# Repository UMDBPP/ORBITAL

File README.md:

# ORBITAL
Stablization System plus more

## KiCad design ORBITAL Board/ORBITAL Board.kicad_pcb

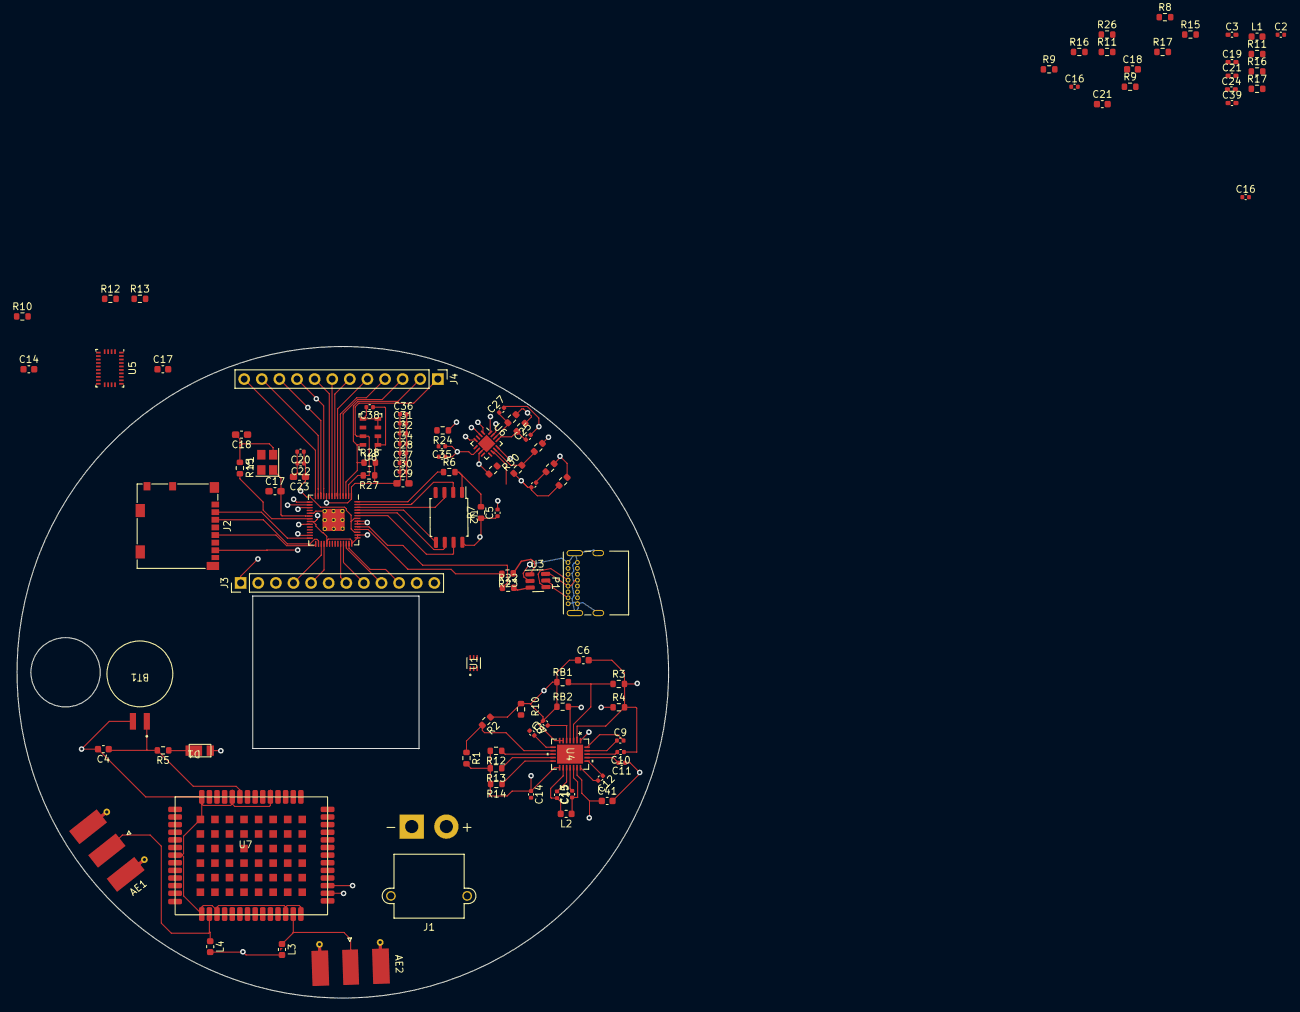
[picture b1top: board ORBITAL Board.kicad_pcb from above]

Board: 4 copper layers, 94.0 x 94.0 mm, 107 parts (0 on the bottom side), 93 nets.

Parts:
AE1, AE2: Antenna; SMA_Molex_73251-1153_EdgeMount_Horizontal
BT1: MS920SE; BT1
C1: 22n; C_0402_1005Metric
C2: 10u; C_0402_1005Metric
C3, C24, C39: 100n; C_0402_1005Metric_Pad0.74x0.62mm_HandSolder
C4: 1u; C_0603_1608Metric
C5, C13, C15, C16#2, C20, C22, C28, C30, C31, C32, C34, C36, C37, C38: 100n; C_0402_1005Metric
C6, C41: 22u; C_0603_1608Metric
C7: 4.7u; C_0402_1005Metric
C8: 1.8n; C_0402_1005Metric
C9, C12, C25: 10n; C_0402_1005Metric
C10, C11: 47n; C_0402_1005Metric
C14: 100u; C_0402_1005Metric
C14#2: 10u; C_0603_1608Metric
C16: 22U; C_0402_1005Metric
C17, C18#2: 22p; C_0603_1608Metric
C17#2, C18: 27p; C_0603_1608Metric_Pad1.08x0.95mm_HandSolder
C19: 22p; C_0402_1005Metric_Pad0.74x0.62mm_HandSolder
C21: 22u; C_0402_1005Metric_Pad0.74x0.62mm_HandSolder
C21#2: 2.2u; C_0603_1608Metric
C23, C29: 1u; C_0603_1608Metric_Pad1.08x0.95mm_HandSolder
C27: 1n; C_0402_1005Metric
C33: 2.2u; C_0402_1005Metric
C35: 22u; C_0402_1005Metric
D1: D_Zener; DFLS130L
J1: Conn_01x02; AMASS_XT30PW-M_1x02_P2.50mm_Horizontal
J2: Micro_SD_Card_Det; microSD_HC_Molex_104031-0811
J3, J4: Conn_01x12; PinHeader_1x12_P2.54mm_Vertical
L1: 4.7u; L_0603_1608Metric
L2: 3.3u; L_0603_1608Metric
L3, L4: 39n; L_0603_1608Metric
P1: USB_C_Plug_USB2.0; USB_C_Receptacle_GCT_USB4085
R1: 500K; R_0603_1608Metric
R2, R16: 100K; R_0603_1608Metric
R3: 350K; R_0603_1608Metric
R4: 510K; R_0603_1608Metric
R5: 620; R_0603_1608Metric
R6, R15#2: 1k; R_0603_1608Metric
R7, R9#2, R17#2, R26, R27, R28: 10k; R_0603_1608Metric
R8, R9: 5.1k; R_0603_1608Metric
R10: 40.2K; R_0603_1608Metric
R10#2, R11, R12#2, R13#2: 2.2k; R_0603_1608Metric
R11#2: 225k; R_0603_1608Metric
R12, R13, R14: 5.1K; R_0603_1608Metric
R15: 1M; R_0603_1608Metric
R16#2: 715k; R_0603_1608Metric
R17: 50k; R_0603_1608Metric
R18, R19: 18; R_0603_1608Metric
R20: 1K; R_0603_1608Metric
R21: 47K; R_0603_1608Metric
R22, R23: 27.4; R_0603_1608Metric
R24, R25: .33; R_0603_1608Metric
R29: 9000; R_0603_1608Metric
R30: 2000; R_0603_1608Metric
RB1, RB2: 100K; R_0603_1608Metric
U1: PTPS563206DRLR; SOT_07SDRLR_TEX
U2: W25Q128JVS; SOIC-8_5.23x5.23mm_P1.27mm
U3: USBLC6-2SC6; SOT-23-6
U4: LTC3118
U5: BNO085; LGA-28_5.2x3.8mm_P0.5mm
U5#2: RP2040; RP2040-QFN-56
U6: STSPIN220; VQFN-16-1EP_3x3mm_P0.5mm_EP1.8x1.8mm
U7: PX1172RH
U8: MS5607-02BA; LGA-8_3x5mm_P1.25mm
Y1: ABLS-12.000MHZ-B4-T; Crystal_SMD_Abracon_ABM8G-4Pin_3.2x2.5mm

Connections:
+1V1: C20.1, C22.1, C23.1, R29.2, U5#2.23 (DVDD), U5#2.45 (VREG_VOUT), U5#2.50 (DVDD)
+3.3V: C5.1, C19.1, C21.2, C24.2, C28.1, C29.1, C30.1, C31.1, C32.1, C34.1, C36.1, C37.1, C38.1, J2.4 (VDD), L1.2, L3.2, L4.2, R7.1, R11#2.2, R18.2, R19.2, R27.1, R28.2, U2.8 (VCC), U5#2.1 (IOVDD), U5#2.10 (IOVDD), U5#2.22 (IOVDD), U5#2.33 (IOVDD), U5#2.42 (IOVDD), U5#2.43 (ADC_AVDD), U5#2.44 (VREG_IN), U5#2.48 (USB_VDD), U5#2.49 (IOVDD), U7.33 (VDD33), U7.34 (VDD33), U8.1 (VDD), U8.2 (PS)
+3V3: D1.2 (A), J3.12, R9#2.1, R10#2.2, R11.1, R12#2.2, R13#2.1, R17#2.1, R26.1, U5.3 (VDD), U5.28 (VDDIO)
+6V: C2.2, C14.1, C33.1, C35.1, C39.1, R1.2, R12.2, R13.2, R14.2, R16.2, U1.1 (VIN), U4.13 (VOUT), U6.6 (VS)
+BATT: C16.2, C41.1, J1.2, U4.18 (VIN2)
/A0: J3.7, U5#2.38 (GPIO26_ADC0)
/A1: J3.8, U5#2.39 (GPIO27_ADC1)
/A2: J3.9, U5#2.40 (GPIO28_ADC2)
/A3: J3.10, U5#2.41 (GPIO29_ADC3)
/D0: J4.1, R27.2, U5#2.2 (GPIO0), U8.7 (SDI/SDA)
/D1: J4.2, R28.1, U5#2.3 (GPIO1), U8.8 (SCLK)
/D2: J4.3, U5#2.4 (GPIO2), U6.16 (MODE1)
/D3: J4.4, U5#2.5 (GPIO3), U6.15 (MODE2)
/D4: J4.5, U5#2.6 (GPIO4), U6.1 (DIR)
/D5: J4.6, U5#2.7 (GPIO5), U6.2 (STCK)
/D6: J4.7, U5#2.8 (GPIO6)
/D7: J4.8, U5#2.9 (GPIO7)
/D8: J4.9, U5#2.11 (GPIO8), U7.16 (RXD_R)
/D9: J4.10, U5#2.12 (GPIO9), U7.17 (TXD_R)
/D10: J4.11, U5#2.13 (GPIO10)
/D11: J4.12, U5#2.14 (GPIO11)
/D12: J3.1, U5#2.15 (GPIO12)
/D13: J3.2, U5#2.16 (GPIO13)
/D14: J3.3, U5#2.17 (GPIO14)
/D15/CLK IN: J3.4, U5#2.31 (GPIO20)
/D16/CLK OUT: J3.5, U5#2.32 (GPIO21)
/D+: R22.2, U3.3 (I/O2)
/D-: R23.1, U3.1 (I/O1)
/QSPI_SCLK: U2.6 (CLK), U5#2.52 (QSPI_SCLK)
/QSPI_SD0: U2.5 (DI(IO0)), U5#2.53 (QSPI_SD0)
/QSPI_SD1: U2.2 (DO(IO1)), U5#2.55 (QSPI_SD1)
/QSPI_SD2: U2.3 (IO2), U5#2.54 (QSPI_SD2)
/QSPI_SD3: U2.7 (IO3), U5#2.51 (QSPI_SD3)
/QSPI_SS: R6.1, U5#2.56 (QSPI_SS)
/RESET: R26.2, U5.11 (NRST), U5#2.26 (RUN)
/SCL: R12#2.1, U5.19 (H_SCL/SCK/RX)
/SDA: R13#2.2, U5.20 (H_SDA/H_MISO/TX)
/SD_CS: J2.2 (DAT3/CD), U5#2.28 (GPIO17)
/SD_DIN: J2.3 (CMD), U5#2.30 (GPIO19)
/SD_DOUT: J2.7 (DAT0), U5#2.27 (GPIO16)
/SD_SCLK: J2.5 (CLK), U5#2.29 (GPIO18)
/VRef: R29.1, R30.2, U6.11 (REF)
/V_BCK: C4.1, R5.2, U7.36 (V_BCKP)
GND: C1.2, C2.1, C4.2, C5.2, C6.1, C7.2, C11.1, C14.2, C14#2.2, C16.1, C16#2.1, C17.2, C17#2.1, C18.1, C18#2.1, C20.2, C21.1, C21#2.2, C22.2, C23.2, C24.1, C25.2, C27.2, C28.2, C29.2, C30.2, C31.2, C32.2, C33.2, C34.2, C35.2, C36.2, C37.2, C38.2, C39.2, C41.2, J1.1, J2.6 (VSS), J2.11 (SHIELD), J3.11, P1.A1 (GND), P1.A12 (GND), P1.B1 (GND), P1.B12 (GND), P1.S1 (SHIELD), R2.1, R8.2, R9.2, R10.1, R16#2.2, R17.1, R21.2, R24.2, R25.2, R30.1, RB1.1, RB2.1, U1.3 (GND), U2.4 (GND), U3.2 (GND), U4.1 (SEL), U4.6 (MODE), U4.7 (GND), U5.2 (GND), U5.5 (PS1), U5.6 (PS0/WAKE), U5.10 (CLKSEL0), U5.14 (H_INTN), U5.17 (SA0/H_MOSI_), U5.25 (GND), U5#2.19 (TESTEN), U5#2.57 (GND), U6.7 (GND), U6.17 (EPAD), U7.1 (GND), U7.1$ (GND), U7.3 (GND), U7.12 (GND), U7.14 (GND), U7.32 (GND), U7.37 (GND), U7.41 (GND), U7.48 (GND), U8.3 (GND), U8.4 (CSB), U8.5 (CSB)
unnamed: AE1.1 (A), L4.1, U7.2 (RF_INI)
unnamed: AE2.1 (A), L3.1, U7.13 (RF_IN2)
unnamed: C1.1, R20.2
unnamed: C8.1, R10.2
unnamed: C16#2.2, U5.9 (CAP)
unnamed: C17.1, U5.26 (XOUT32/CLKSEL1)
unnamed: C18.2, C18#2.2, R15#2.1, U5.27 (XIN32), Y1.2
unnamed: D1.1 (K), R5.1
unnamed: P1.A5 (CC1), R8.1
unnamed: P1.B5 (CC2), R9.1
unnamed: P1.A6 (D+), P1.B6 (D+), U3.6 (I/O1)
unnamed: P1.A7 (D-), P1.B7 (D-), U3.4 (I/O2)
unnamed: R10#2.1, U5.15 (ENV_SCL)
unnamed: R11.2, U5.16 (ENV_SDA)
unnamed: R15.2, R16#2.1
unnamed: R17#2.2, U5.4 (BOOTN)
unnamed: C3.1, U1.4 (BST)
unnamed: R16.1, U1.5 (EN)
unnamed: C19.2, R11#2.1, R17.2, U1.6 (FB)
unnamed: C3.2, L1.1, U1.2 (SW)
unnamed: R6.2, R7.2, U2.1 (~CS)
unnamed: C13.2, U4.16 (BST1)
unnamed: C15.1, U4.15 (BST2)
unnamed: C10.2, U4.22 (CM1)
unnamed: C11.2, U4.21 (CM2)
unnamed: C9.1, U4.23 (CN1)
unnamed: C12.1, U4.20 (CN2)
unnamed: C9.2, U4.24 (CP1)
unnamed: C12.2, U4.19 (CP2)
unnamed: R1.1, R2.2, U4.9 (FB)
unnamed: R14.1, U4.12 (PGD)
unnamed: R3.1, RB1.2, U4.3 (RUN1)
unnamed: R4.1, RB2.2, U4.4 (RUN2)
unnamed: C13.1, L2.1, U4.17 (SW1)
unnamed: C15.2, L2.2, U4.14 (SW2)
unnamed: R12.1, U4.10 (V1GD)
unnamed: R13.1, U4.11 (V2GD)
unnamed: C8.2, U4.8 (VC)
unnamed: C7.1, U4.5 (VCC)
unnamed: R23.2, U5#2.46 (USB_DM)
unnamed: R22.1, U5#2.47 (USB_DP)
unnamed: C17#2.2, U5#2.20 (XIN), Y1.1
unnamed: R15#2.2, U5#2.21 (XOUT)
unnamed: C25.1, R18.1, U6.13 (EN/FLT)
unnamed: R24.1, U6.4 (SENSEA)
unnamed: R25.1, U6.9 (SENSEB)
unnamed: C27.1, R19.1, U6.14 (STBY/RESET)
unnamed: R20.1, R21.1, U6.12 (TOFF)
VBUS: C6.2, C10.1, C21#2.1, P1.A4 (VBUS), P1.A9 (VBUS), P1.B4 (VBUS), P1.B9 (VBUS), R3.2, R4.2, R15.1, U3.5 (VBUS), U4.2 (VIN1)

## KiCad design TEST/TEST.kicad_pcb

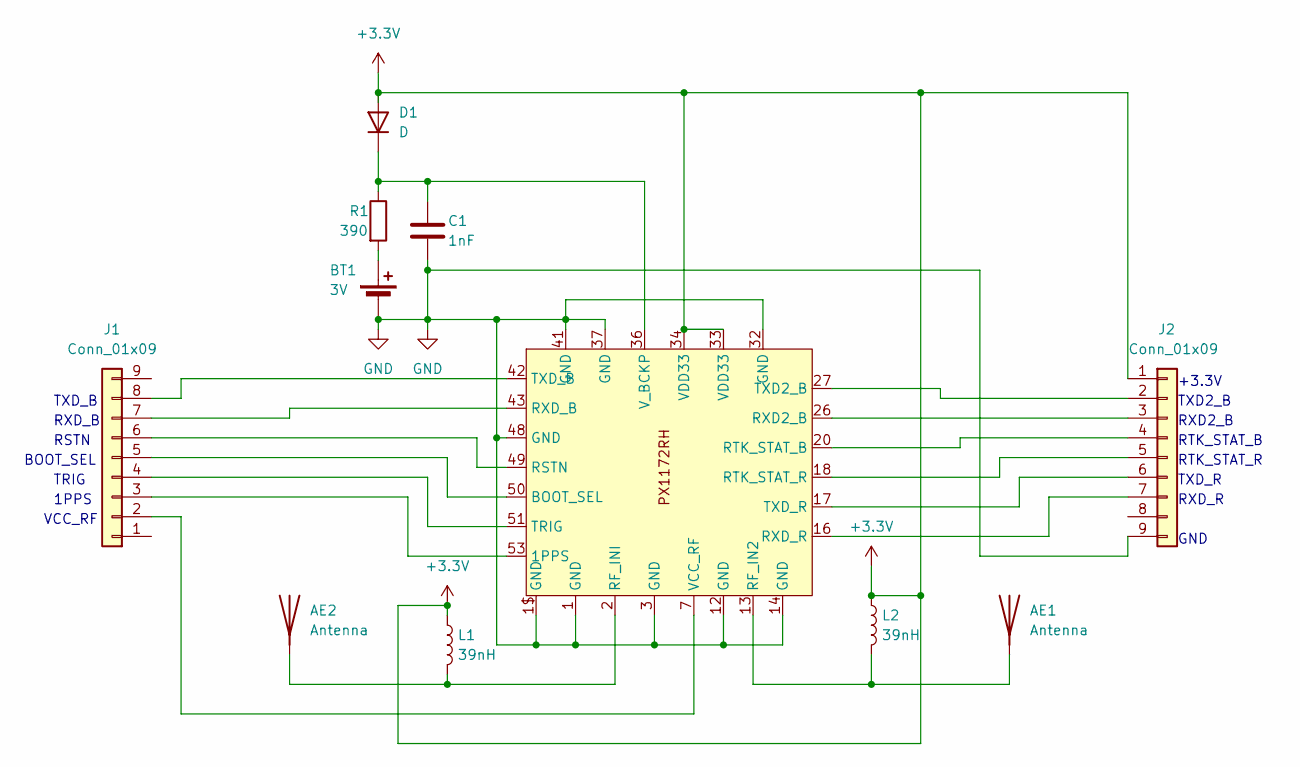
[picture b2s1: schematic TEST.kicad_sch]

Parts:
AE1, AE2: Antenna; SMA_Molex_73251-1153_EdgeMount_Horizontal
BT1: 3V; BAT_MS920SE-FL27E
C1: 1nF; C_0402_1005Metric
D1: D; DFLS130L
J1, J2: Conn_01x09; PinSocket_1x09_P2.54mm_Vertical
L1, L2: 39nH; L_0402_1005Metric
R1: 390; R_0402_1005Metric
U1: PX1172RH

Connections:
+3.3V: D1.2 (A), J2.1, L1.1, L2.1, U1.33 (VDD33), U1.34 (VDD33)
GND: BT1.N (-), C1.2, J2.9, U1.1 (GND), U1.1$ (GND), U1.3 (GND), U1.12 (GND), U1.14 (GND), U1.32 (GND), U1.37 (GND), U1.41 (GND), U1.48 (GND)
unnamed: AE1.1 (A), L2.2, U1.13 (RF_IN2)
unnamed: AE2.1 (A), L1.2, U1.2 (RF_INI)
unnamed: BT1.P (+), R1.2
unnamed: C1.1, D1.1 (K), R1.1, U1.36 (V_BCKP)
unnamed: J1.2, U1.7 (VCC_RF)
unnamed: J1.3, U1.53 (1PPS)
unnamed: J1.4, U1.51 (TRIG)
unnamed: J1.5, U1.50 (BOOT_SEL)
unnamed: J1.6, U1.49 (RSTN)
unnamed: J1.7, U1.43 (RXD_B)
unnamed: J1.8, U1.42 (TXD_B)
unnamed: J2.2, U1.27 (TXD2_B)
unnamed: J2.3, U1.26 (RXD2_B)
unnamed: J2.4, U1.20 (RTK_STAT_B)
unnamed: J2.5, U1.18 (RTK_STAT_R)
unnamed: J2.6, U1.17 (TXD_R)
unnamed: J2.7, U1.16 (RXD_R)

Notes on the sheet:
RSTN
TXD_B
RTK_STAT_R
RXD_R
BOOT_SEL
RTK_STAT_B
VCC_RF
RXD2_B
1PPS
TXD2_B
RXD_B
GND
TXD_R
TRIG
+3.3V

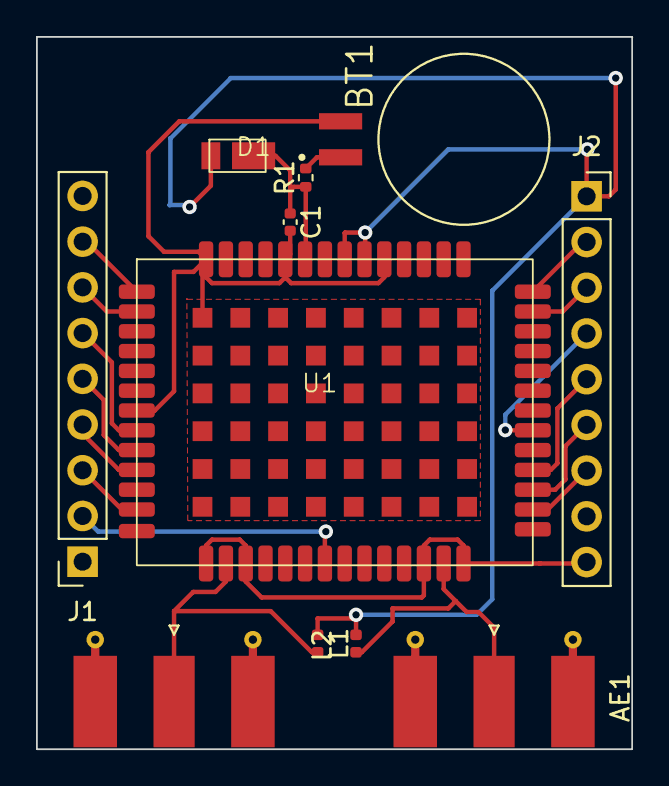
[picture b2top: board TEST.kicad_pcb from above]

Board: 2 copper layers, 33.1 x 39.6 mm, 11 parts (0 on the bottom side), 19 nets.

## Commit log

2024-02-06 Board upload
2024-02-06 sims
2024-02-27 Uploading Board Progress
2024-03-01 Adding schematic and PCB updates
2024-03-05 Updating board + adding in board notes
2024-03-07 Updating SD Card to enable SPI comms. with RP2040
2024-03-07 Creating .2V Vref source for motor controller
2024-03-12 Updating PCB Layout
2024-03-12 Updating PCB
2024-03-26 Updating ORBITAL PCB
2024-03-27 Implementing Motor Controller into PCB
2024-03-27 Adding in LTC3118 to PCB
